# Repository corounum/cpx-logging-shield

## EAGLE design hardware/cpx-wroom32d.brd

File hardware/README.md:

## CPX Logging Shield

This "shield" for the Circuit Playground Express integrates:

* an ESP32 WROOM-32D module for capturing data via serial (or, eventually, I2C), storing that data (on the integrated 4MB flash), and presenting the data back via WiFi
* A BME680 temperature/pressure/VOC/eCO2 sensor
* A PCF8523 real time clock (for timestamping readings) and CR1220 battery (for clock retention)

In addition, a QUIIC connector is included for attaching Sparkfun-produced I2C modules. The bottom-mounted FTDI header can be soldered for development, and used as pogopin landing pads for production with the appropriate jig.

The board ONLY takes power from a connected CPX; it draws from VOUT, which is EITHER connected to USB or battery. The shield has its own AP2112 voltage regulator.

It is expected that the combination of a CPX and this shield might run for at most days. The shield attempts to sleep between readings, but it is known that this is potentially a "short life" sensing platform suitable for educational purposes, but not long-life monitoring in research contexts.

The following README text acknowledges that the board design herein leverages the excellent work of [Adafruit Industries](https://adafruit.com), and as a derivative work, is provided under a compatible, open license.

## Adafruit-Circuit-Playground-Express-PCB

PCB files for the Adafruit Circuit Playground Express

This is the PCB files for the Adafruit Circuit Playground
Format is EagleCAD schematic and board layout

For more details, check out the product page at

   * http://www.adafruit.com/products/3333

Adafruit invests time and resources providing this open source design, 
please support Adafruit and open-source hardware by purchasing 
products from Adafruit!

Designed by Adafruit Industries.  
Creative Commons Attribution, Share-Alike license, check license.txt for more information
All text above must be included in any redistribution

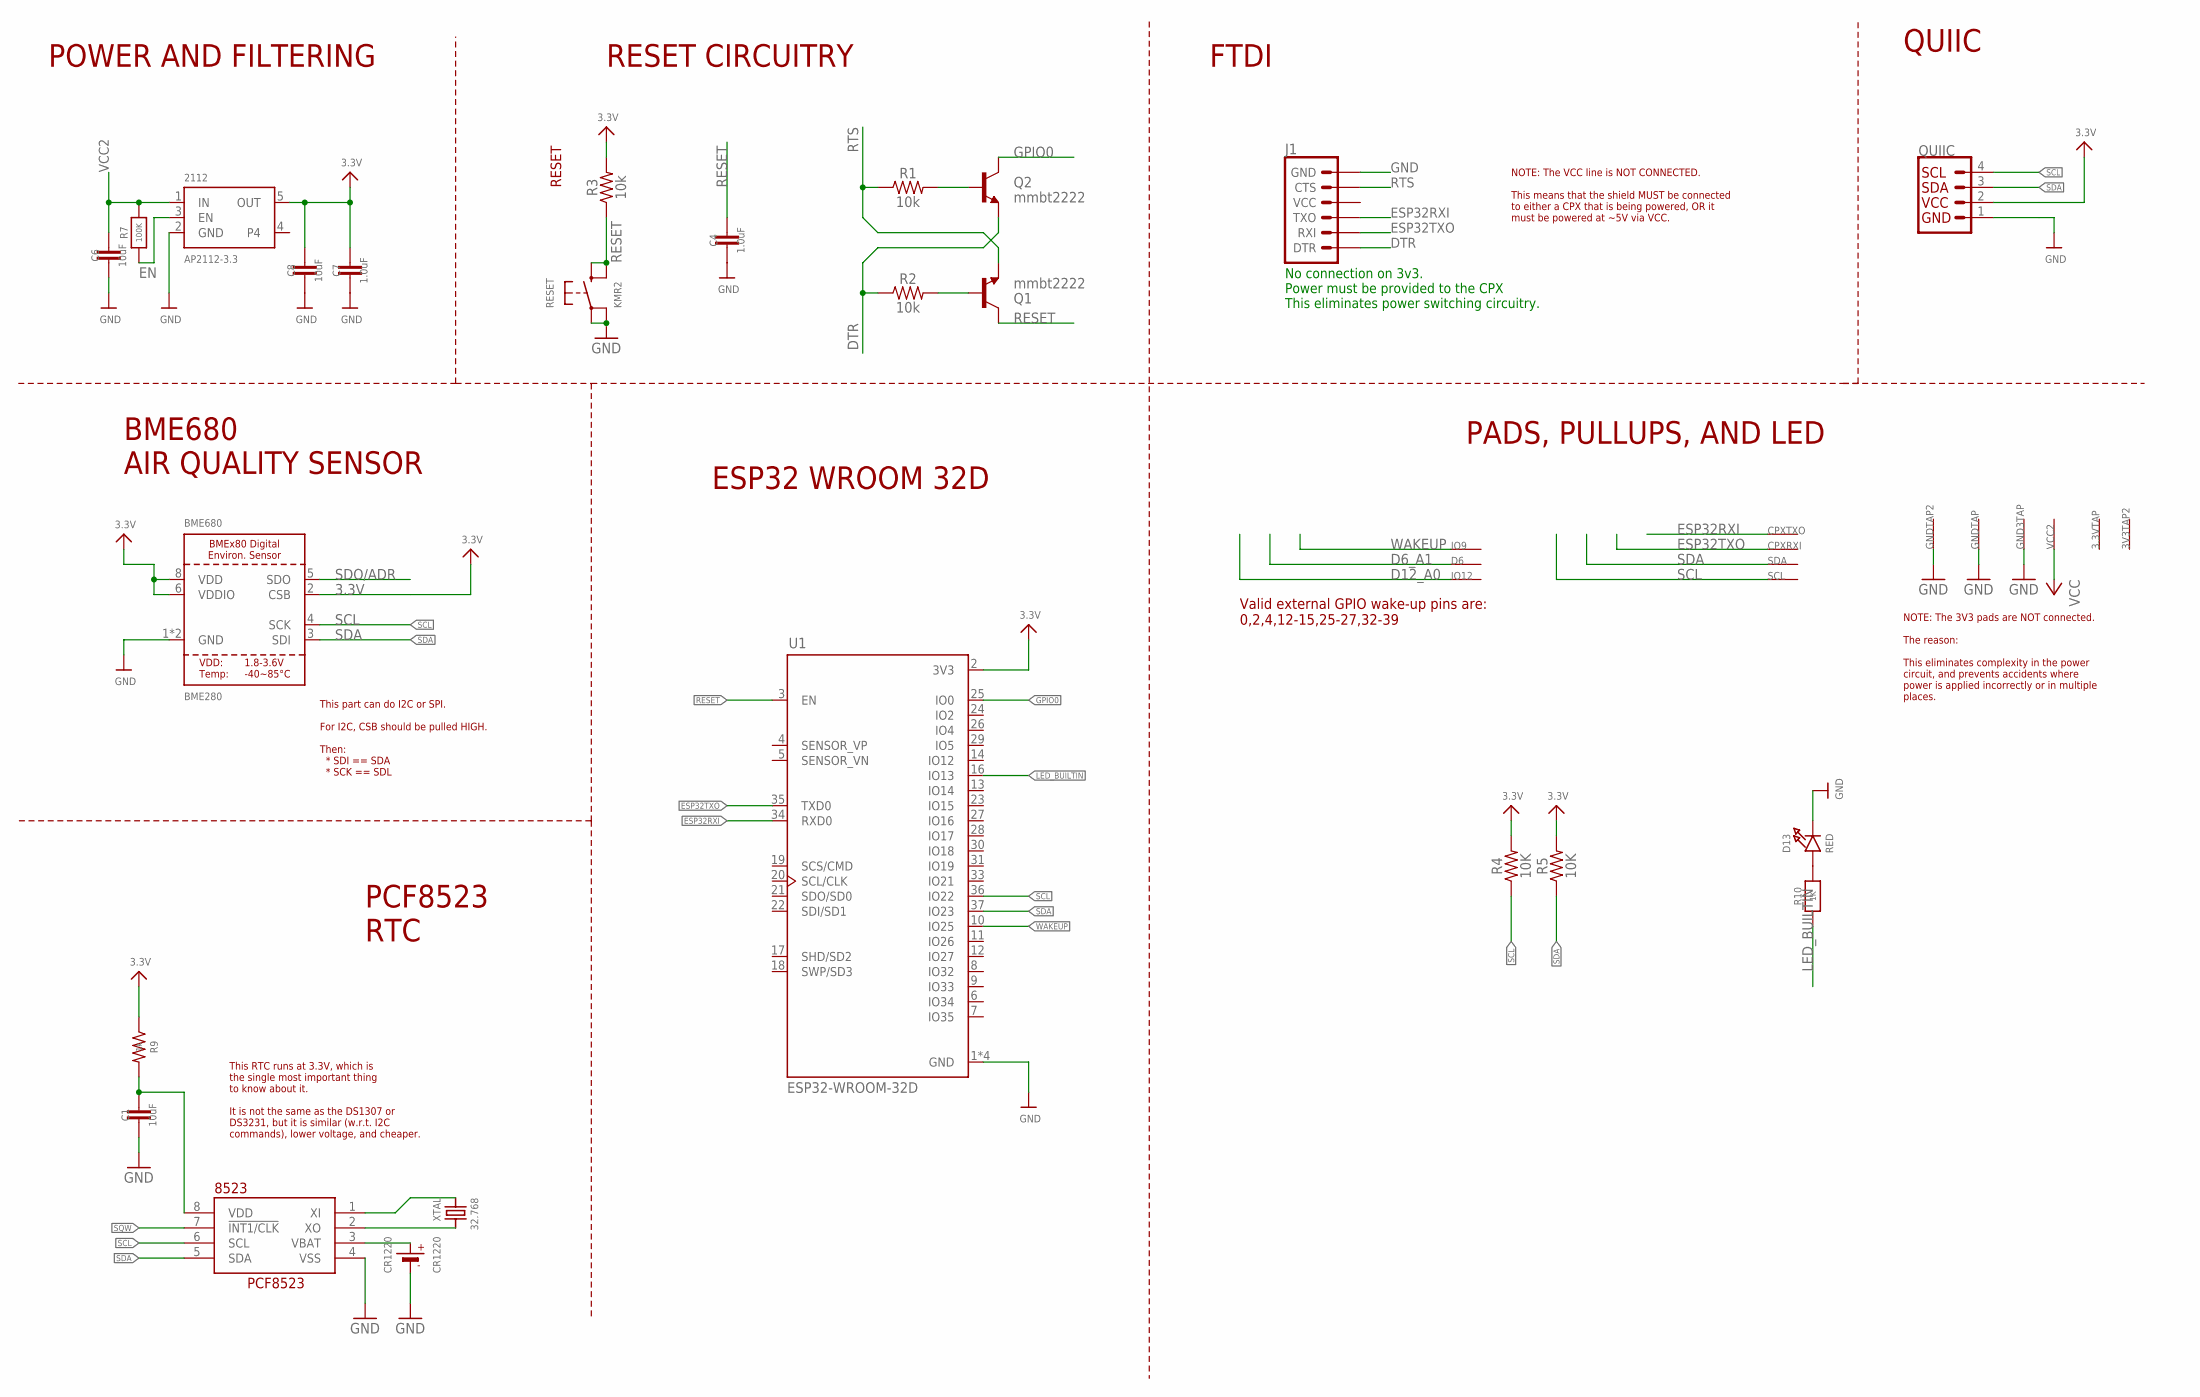
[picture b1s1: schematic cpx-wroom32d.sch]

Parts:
3.3VTAP, 3V3TAP2: SEWTAP-ALLIGATOR; SEWALLI
2112: AP2112-3.3; SOT23-5
8523: RTC_PCF8523T; SOIC8_150MIL
BME680: BME280
C1, C6, C8: 10uF; 0603
C4, C7: 1.0uF; 0603
CPXRXI: SEWTAP-ALLIGATOR; SEWALLI
CPXTXO: SEWTAP-ALLIGATOR; SEWALLI
CR1220: CR1220
D6: SEWTAP-ALLIGATOR; SEWALLI
D13: RED; CHIPLED_0805_NOOUTLINE
GND3TAP: SEWTAP-ALLIGATOR; SEWALLI
GNDTAP, GNDTAP2: SEWTAP-ALLIGATOR; SEWALLI
IO9, IO12: SEWTAP-ALLIGATOR; SEWALLI
J1: 6_PIN_SERIAL_TARGETRA_SMT; 6_PIN_SERIAL_TARGET_SIDE_RA_SMT
Q1, Q2: mmbt2222; SOT23-3
QUIIC: QWIIC_CONNECTORJS-1MM; 1X04_1MM_RA
R1, R2, R3: 10k; 0603
R4, R5: 10K; 0603
R7: 100K; 0603-NO
R9: 1k; 0603
R10: 1K; 0603-NO
RESET: KMR2; BTN_KMR2_4.6X2.8
SCL: SEWTAP-ALLIGATOR; SEWALLI
SDA: SEWTAP-ALLIGATOR; SEWALLI
U1: ESP32-WROOM-32D; MODULE_ESP32-WROOM-32D
VCC2: SEWTAP-ALLIGATOR; SEWALLI
XTAL: 32.768; CRYSTAL_8X3.8

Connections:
3.3V: 2112.5 (OUT), BME680.2 (CSB), BME680.6 (VDDIO), BME680.8 (VDD), C7.1, C8.1, QUIIC.2 (VCC), R3.2, R4.2, R5.2, R9.1, U1.2 (3V3)
CLKVCC: 8523.8 (VDD), C1.1, R9.2
D6_A1: D6.P$1
D12_A0: IO12.P$1
DTR: J1.1 (DTR), Q2.2 (E), R2.1
EN: 2112.3 (EN), R7.1
ESP32RXI: CPXTXO.P$1, J1.2 (TXO), U1.34 (RXD0)
ESP32TXO: CPXRXI.P$1, J1.3 (RXI), U1.35 (TXD0)
GND: 2112.2 (GND), 8523.4 (VSS), BME680.1 (GND), BME680.7 (GND), C1.2, C4.2, C6.2, C7.2, C8.2, CR1220.-, D13.C, GND3TAP.P$1, GNDTAP.P$1, GNDTAP2.P$1, J1.6 (GND), QUIIC.1 (GND), RESET.A, RESET.A' (P1), U1.1 (GND), U1.15 (GND), U1.38 (GND), U1.39 (GND)
GPIO0: Q2.3 (C), U1.25 (IO0)
LED_BUILTIN: R10.1, U1.16 (IO13)
unnamed: D13.A, R10.2
unnamed: Q1.1 (B), R2.2
unnamed: Q2.1 (B), R1.2
RESET: C4.1, Q1.3 (C), R3.1, RESET.B (S), RESET.B' (S1), U1.3 (EN)
RTS: J1.5 (CTS), Q1.2 (E), R1.1
SCL: 8523.6 (SCL), BME680.4 (SCK), QUIIC.4 (SCL), R4.1, SCL.P$1, U1.36 (IO22)
SDA: 8523.5 (SDA), BME680.3 (SDI), QUIIC.3 (SDA), R5.1, SDA.P$1, U1.37 (IO23)
SDO/ADR: BME680.5 (SDO)
SQW: 8523.7 (!INT1/CLK)
VBAT1: 8523.3 (VBAT), CR1220.+$1 (+)
VCC: VCC2.P$1
VCC2: 2112.1 (IN), C6.1, R7.2
WAKEUP: IO9.P$1, U1.10 (IO25)
XI: 8523.1 (XI), XTAL.P$1 (1)
XO: 8523.2 (XO), XTAL.P$4 (2)

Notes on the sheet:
RESET
No connection on 3v3. Power must be provided to the CPX This eliminates power switching circuitry.
POWER AND FILTERING
RESET CIRCUITRY
FTDI
ESP32 WROOM 32D
BME680 AIR QUALITY SENSOR
PCF8523 RTC
PADS, PULLUPS, AND LED
This part can do I2C or SPI. For I2C, CSB should be pulled HIGH. Then: * SDI == SDA * SCK == SDL
This RTC runs at 3.3V, which is the single most important thing to know about it. It is not the same as the DS1307 or DS3231, but it is similar (w.r.t. I2C commands), lower voltage, and cheaper.
NOTE: The VCC line is NOT CONNECTED. This means that the shield MUST be connected to either a CPX that is being powered, OR it must be powered at ~5V via VCC.
NOTE: The 3V3 pads are NOT connected. The reason: This eliminates complexity in the power circuit, and prevents accidents where power is applied incorrectly or in multiple places.
QUIIC
Valid external GPIO wake-up pins are: 0,2,4,12-15,25-27,32-39

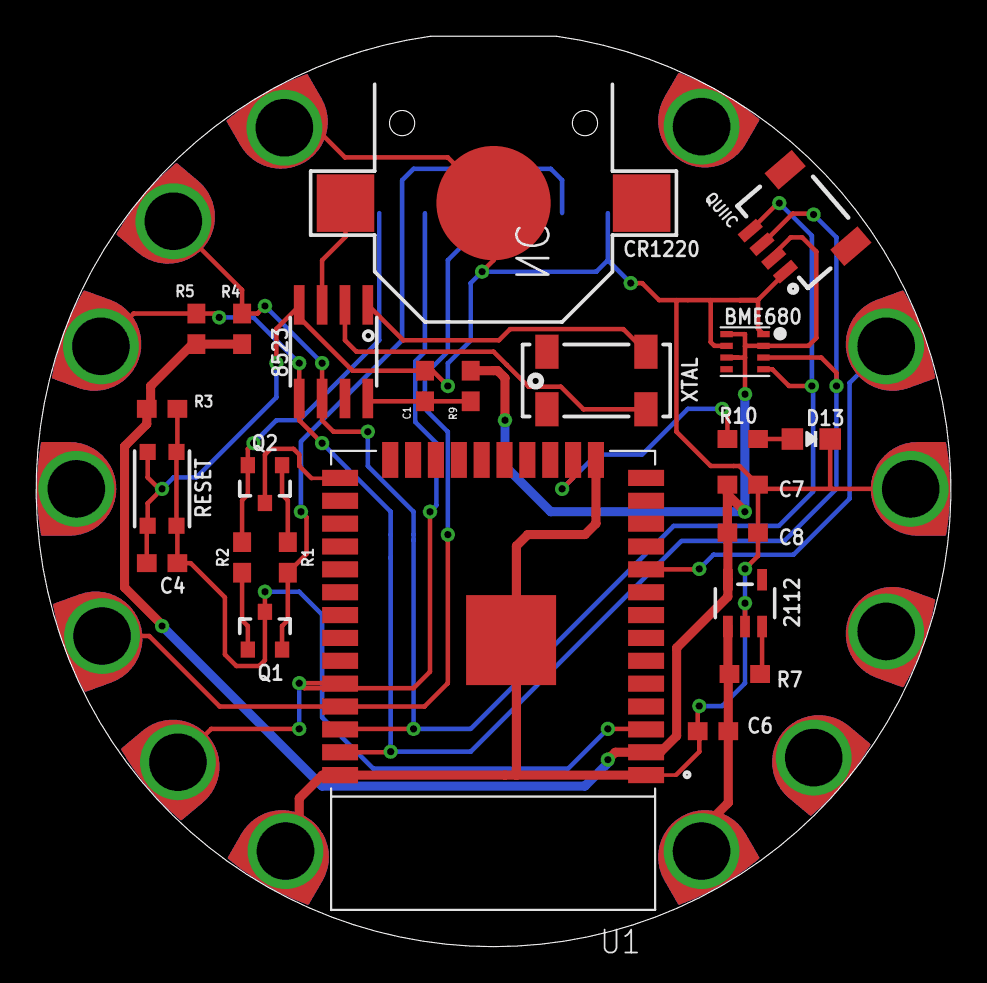
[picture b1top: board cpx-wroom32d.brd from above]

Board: 2 copper layers, 50.8 x 50.6 mm, 38 parts (1 on the bottom side), 21 nets.

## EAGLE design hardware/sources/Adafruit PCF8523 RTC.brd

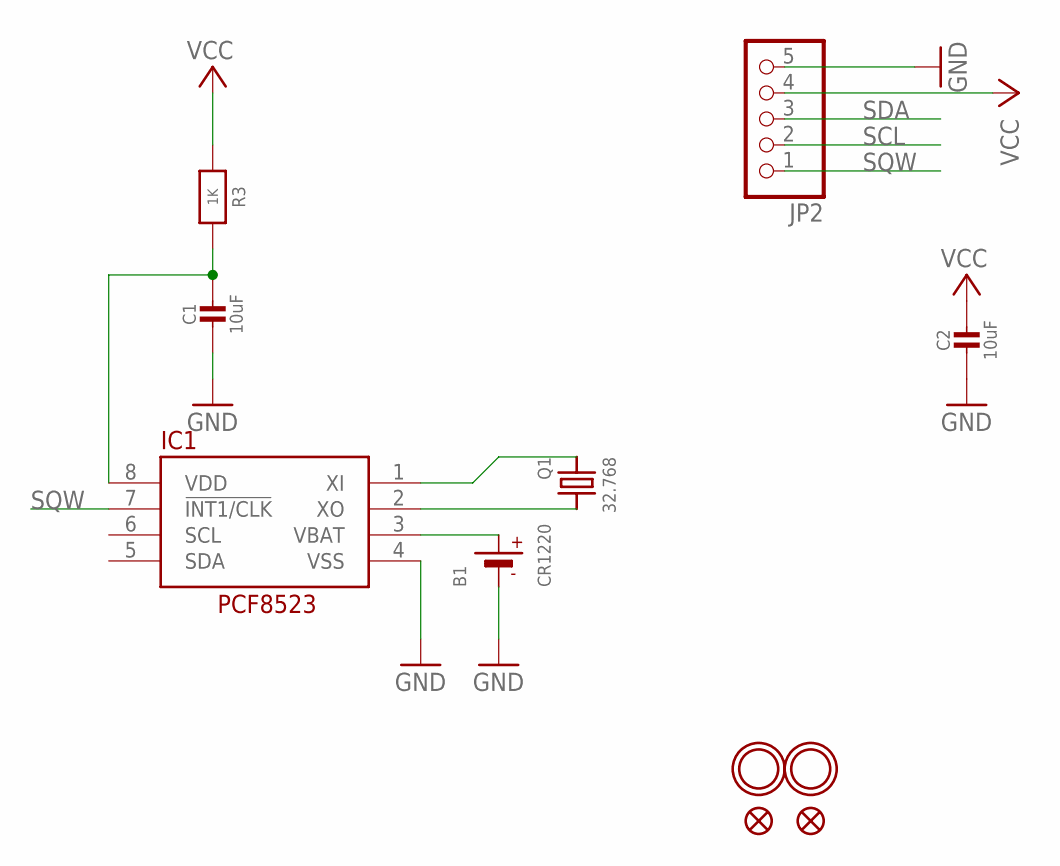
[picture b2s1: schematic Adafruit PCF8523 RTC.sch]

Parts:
B1: CR1220
C1, C2: 10uF; 0805-NO
FID1, FID2: FIDUCIAL""; FIDUCIAL_1MM
IC1: RTC_PCF8523T; SOIC8_150MIL
JP2: HEADER-1X576MIL; 1X05_ROUND_76
Q1: 32.768; CRYSTAL_8X3.8
R3: 1K; 0805-NO
U$1, U$4: MOUNTINGHOLE2.0; MOUNTINGHOLE_2.0_PLATED

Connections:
GND: B1.-, C1.2, C2.2, IC1.4 (VSS), JP2.5
unnamed: C1.1, IC1.8 (VDD), R3.2
unnamed: IC1.1 (XI), Q1.P$1 (1)
unnamed: IC1.2 (XO), Q1.P$4 (2)
SCL: JP2.2
SDA: JP2.3
SQW: IC1.7 (!INT1/CLK), JP2.1
VBAT: B1.+$1 (+), IC1.3 (VBAT)
VCC: C2.1, JP2.4, R3.1

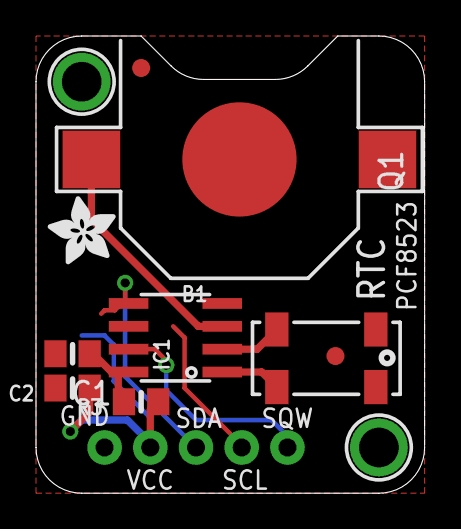
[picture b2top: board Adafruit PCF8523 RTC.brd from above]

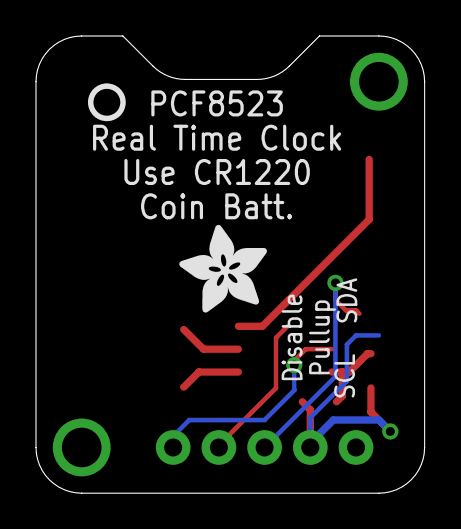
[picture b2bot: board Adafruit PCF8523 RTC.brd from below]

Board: 2 copper layers, 21.6 x 25.4 mm, 14 parts (2 on the bottom side), 7 nets.

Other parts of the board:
U$2: ADAFRUIT_3.5MM
U$3: PCBFEAT-REV-040
U$5: ADAFRUIT_5MM

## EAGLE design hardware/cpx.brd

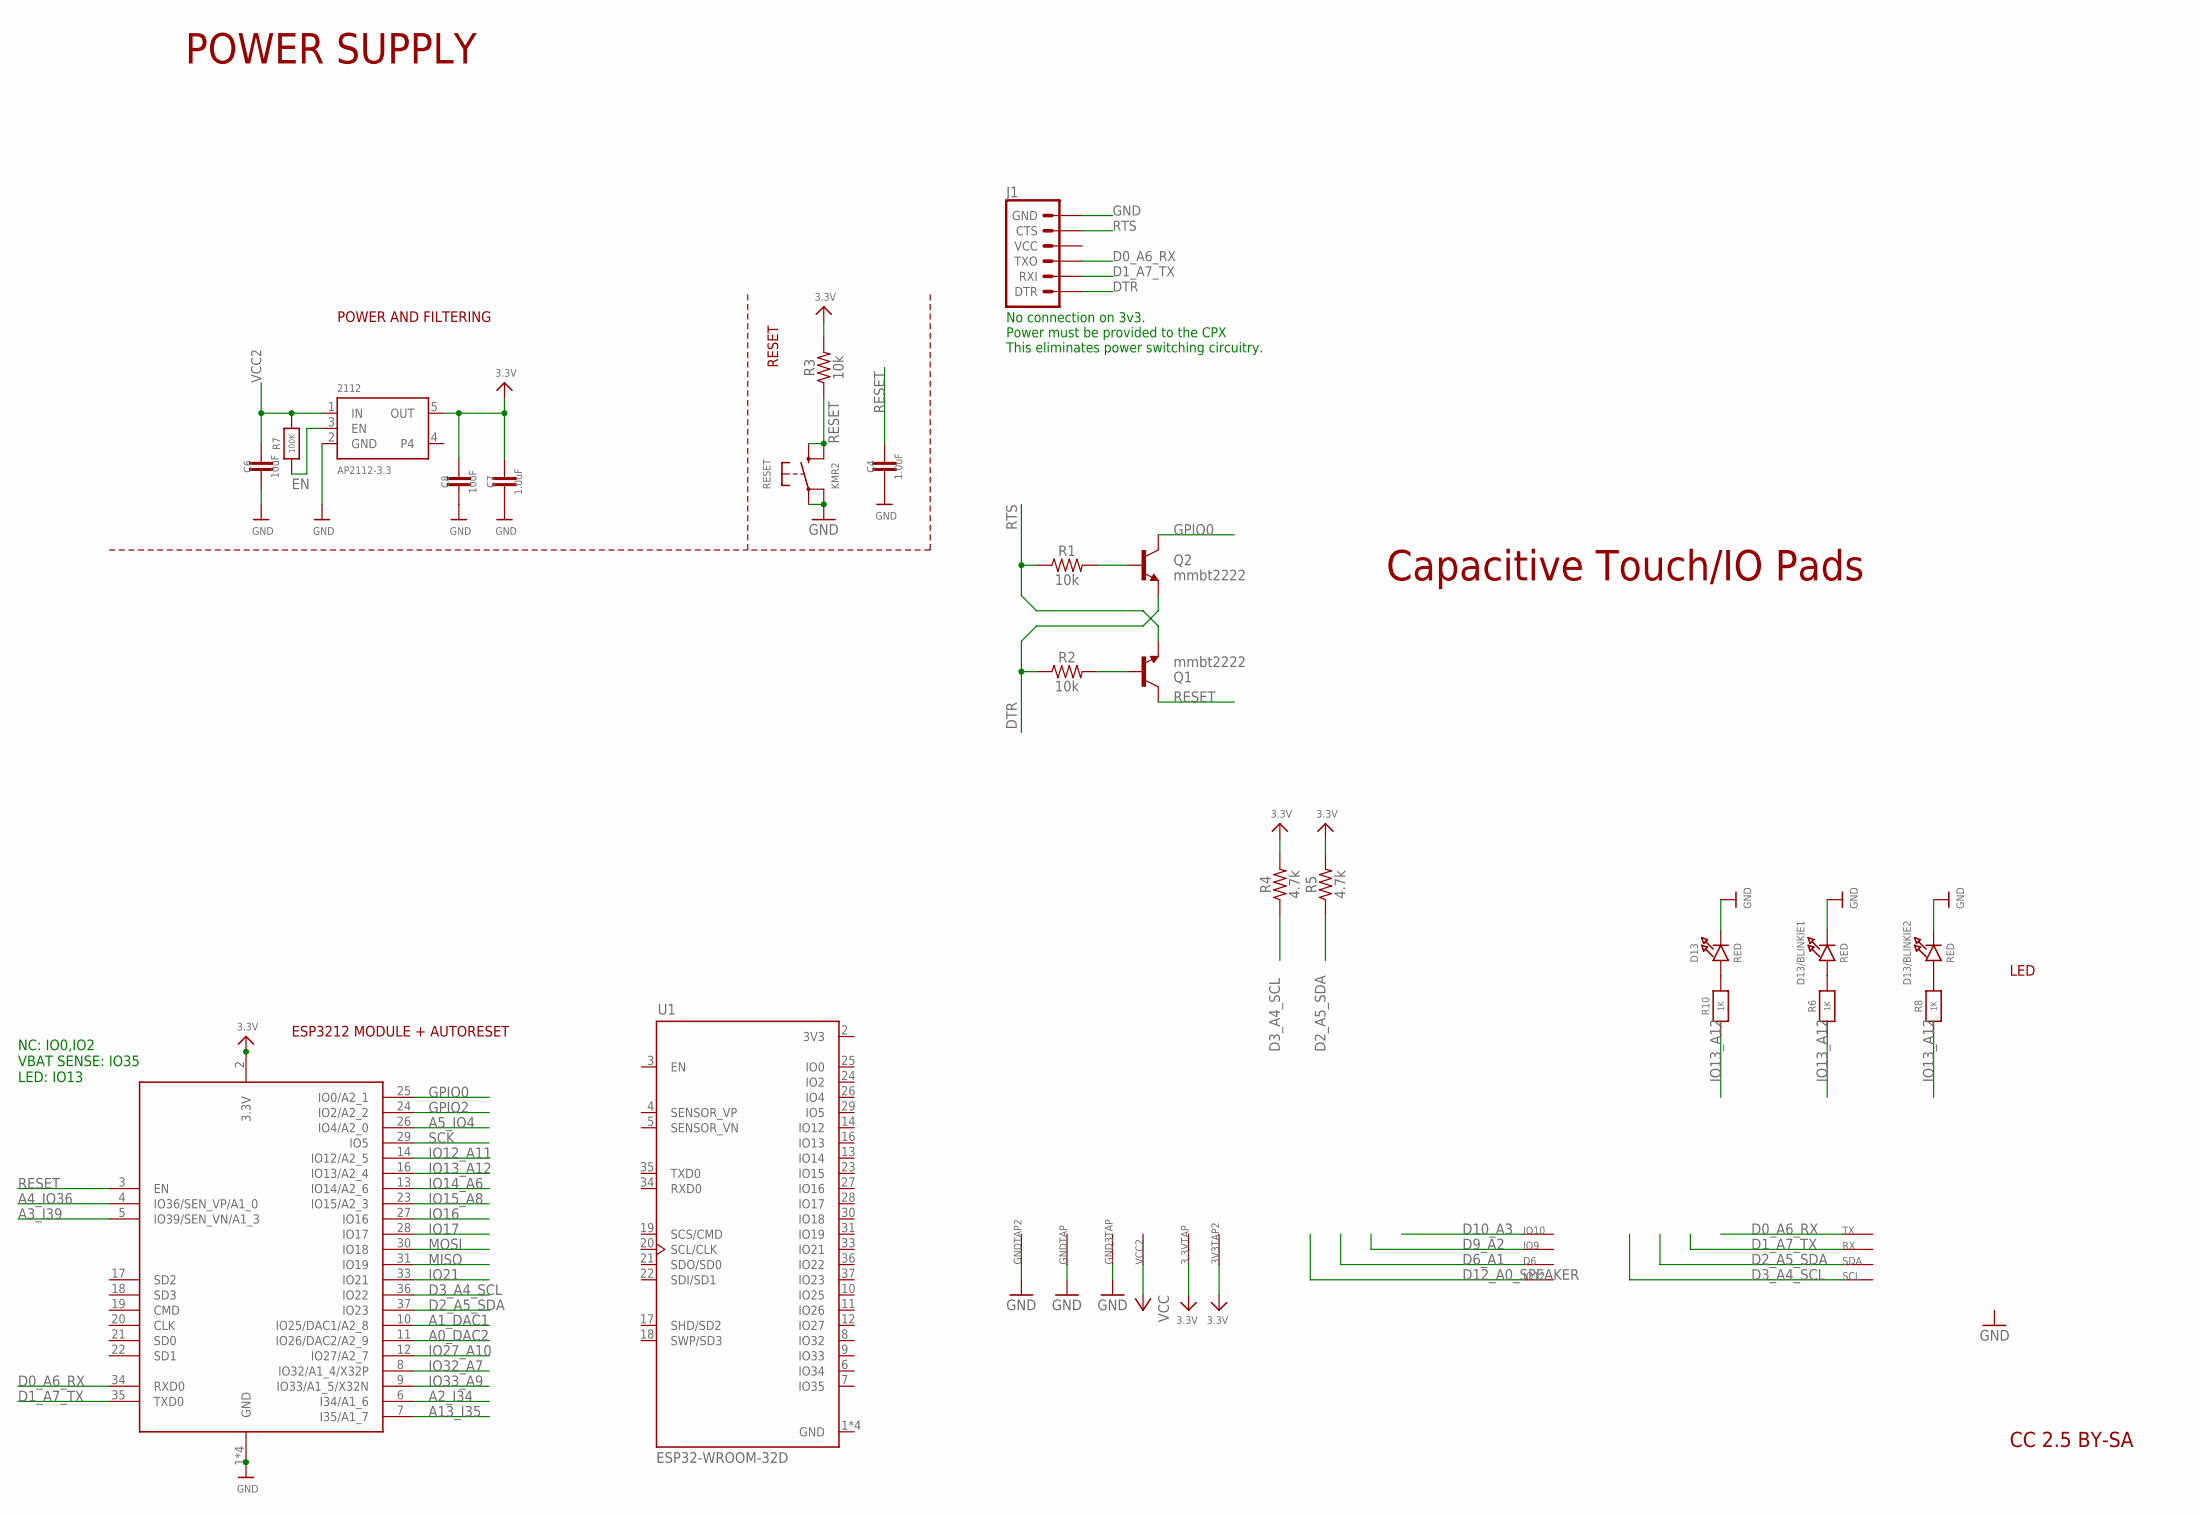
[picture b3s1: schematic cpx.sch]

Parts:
3.3VTAP, 3V3TAP2: SEWTAP-ALLIGATOR; SEWALLI
2112: AP2112-3.3; SOT23-5
C4, C7: 1.0uF; 0603
C6, C8: 10uF; 0603
D6: SEWTAP-ALLIGATOR; SEWALLI
D13, D13/BLINKIE1, D13/BLINKIE2: RED; CHIPLED_0805_NOOUTLINE
GND3TAP: SEWTAP-ALLIGATOR; SEWALLI
GNDTAP, GNDTAP2: SEWTAP-ALLIGATOR; SEWALLI
IO9, IO10, IO12: SEWTAP-ALLIGATOR; SEWALLI
J1: 6_PIN_SERIAL_TARGET; 1X06
Q1, Q2: mmbt2222; SOT23-3
R1, R2, R3: 10k; 0603
R4, R5: 4.7k; 0603
R6, R8, R10: 1K; 0603-NO
R7: 100K; 0603-NO
RESET: KMR2; BTN_KMR2_4.6X2.8
RX: SEWTAP-ALLIGATOR; SEWALLI
SCL: SEWTAP-ALLIGATOR; SEWALLI
SDA: SEWTAP-ALLIGATOR; SEWALLI
TX: SEWTAP-ALLIGATOR; SEWALLI
U1: ESP32-WROOM-32D; MODULE_ESP32-WROOM-32D
VCC2: SEWTAP-ALLIGATOR; SEWALLI
X2: ESP32_WROOM32_SKINNY; WROOM32_SKINNY

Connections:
3.3V: 3.3VTAP.P$1, 3V3TAP2.P$1, 2112.5 (OUT), C7.1, C8.1, R3.2, R4.2, R5.2, X2.2 (3.3V)
3V3: U1.2 (3V3)
A0_DAC2: X2.11 (IO26/DAC2/A2_9)
A1_DAC1: X2.10 (IO25/DAC1/A2_8)
A2_I34: X2.6 (I34/A1_6)
A3_I39: X2.5 (IO39/SEN_VN/A1_3)
A4_IO36: X2.4 (IO36/SEN_VP/A1_0)
A5_IO4: X2.26 (IO4/A2_0)
A13_I35: X2.7 (I35/A1_7)
D0_A6_RX: J1.3 (TXO), TX.P$1, X2.34 (RXD0)
D1_A7_TX: J1.2 (RXI), RX.P$1, X2.35 (TXD0)
D2_A5_SDA: R5.1, SDA.P$1, X2.37 (IO23)
D3_A4_SCL: R4.1, SCL.P$1, X2.36 (IO22)
D6_A1: D6.P$1
D9_A2: IO9.P$1
D10_A3: IO10.P$1
D12_A0_SPEAKER: IO12.P$1
DTR: J1.1 (DTR), Q2.2 (E), R2.1
EN: 2112.3 (EN), R7.1
GND: 2112.2 (GND), C4.2, C6.2, C7.2, C8.2, D13.C, D13/BLINKIE1.C, D13/BLINKIE2.C, GND3TAP.P$1, GNDTAP.P$1, GNDTAP2.P$1, J1.6 (GND), RESET.A, RESET.A' (P1), U1.1 (GND), U1.15 (GND), U1.38 (GND), U1.39 (GND), X2.1 (GND), X2.15 (GND), X2.38 (GND), X2.P$1 (GND)
GPIO0: Q2.3 (C), X2.25 (IO0/A2_1)
GPIO2: X2.24 (IO2/A2_2)
IO12_A11: X2.14 (IO12/A2_5)
IO13_A12: R6.1, R8.1, R10.1, X2.16 (IO13/A2_4)
IO14_A6: X2.13 (IO14/A2_6)
IO15_A8: X2.23 (IO15/A2_3)
IO16: X2.27 (IO16)
IO17: X2.28 (IO17)
IO21: X2.33 (IO21)
IO27_A10: X2.12 (IO27/A2_7)
IO32_A7: X2.8 (IO32/A1_4/X32P)
IO33_A9: X2.9 (IO33/A1_5/X32N)
MISO: X2.31 (IO19)
MOSI: X2.30 (IO18)
unnamed: D13/BLINKIE1.A, R6.2
unnamed: D13/BLINKIE2.A, R8.2
unnamed: D13.A, R10.2
unnamed: Q1.1 (B), R2.2
unnamed: Q2.1 (B), R1.2
RESET: C4.1, Q1.3 (C), R3.1, RESET.B (S), RESET.B' (S1), X2.3 (EN)
RTS: J1.5 (CTS), Q1.2 (E), R1.1
SCK: X2.29 (IO5)
VCC: VCC2.P$1
VCC2: 2112.1 (IN), C6.1, R7.2

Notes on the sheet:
CC 2.5 BY-SA
POWER SUPPLY
Capacitive Touch/IO Pads
POWER AND FILTERING
RESET
LED
ESP3212 MODULE + AUTORESET
NC: IO0,IO2 VBAT SENSE: IO35 LED: IO13
No connection on 3v3. Power must be provided to the CPX This eliminates power switching circuitry.

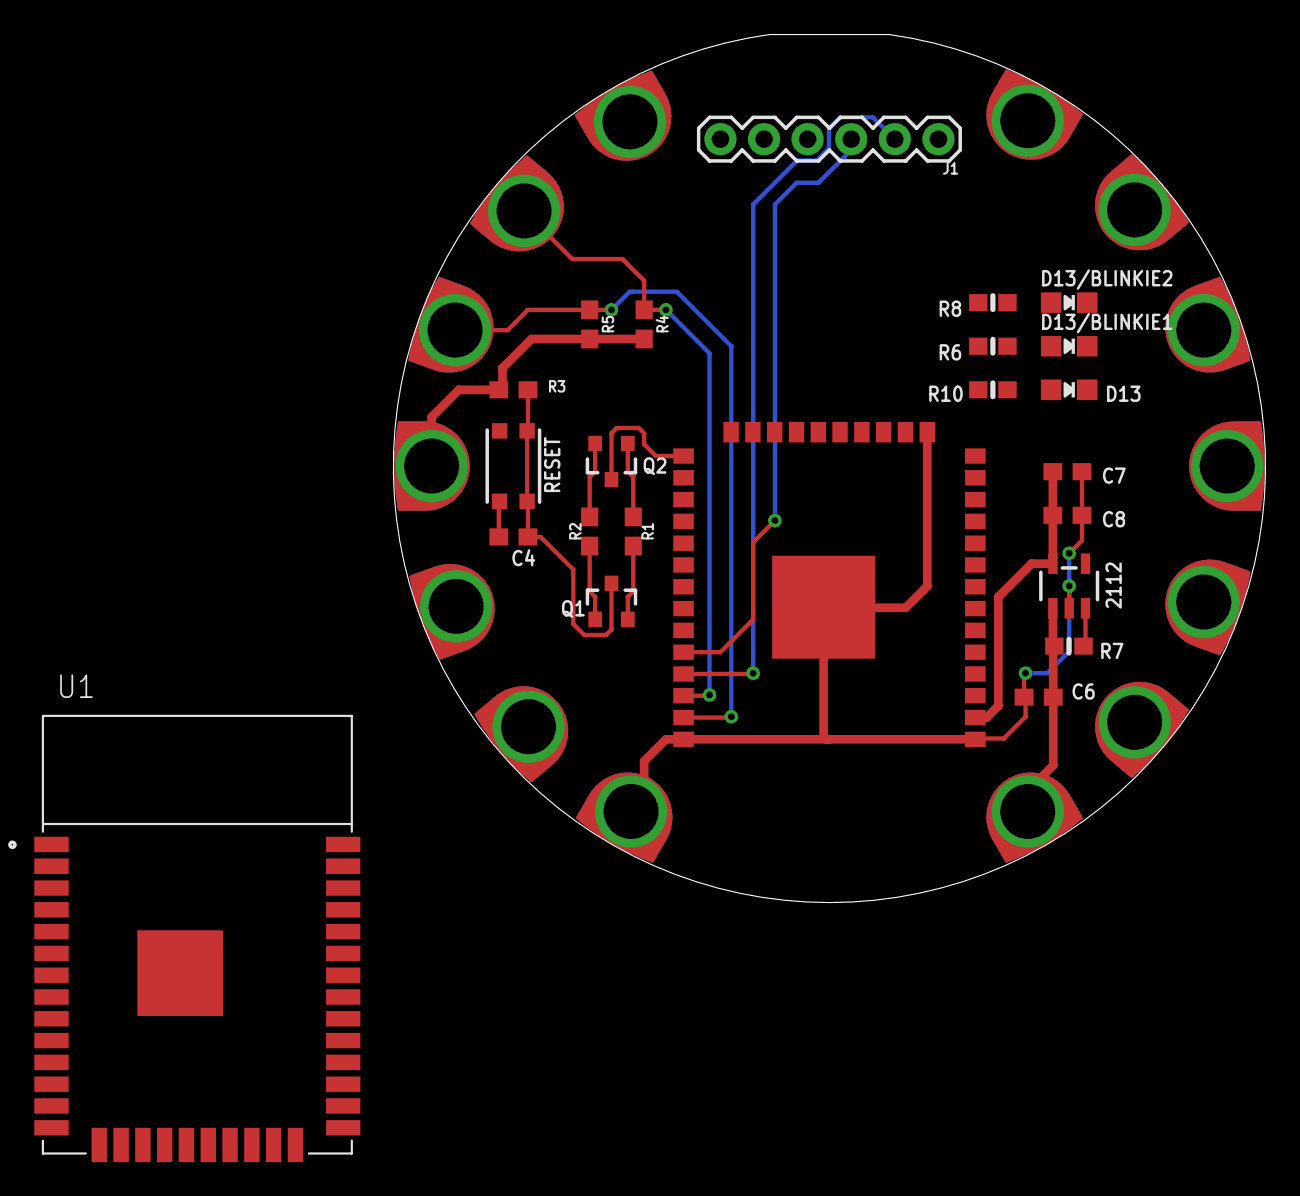
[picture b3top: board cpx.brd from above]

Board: 2 copper layers, 50.8 x 50.6 mm, 39 parts (1 on the bottom side), 18 nets.

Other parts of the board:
U$16: CPLAY_EXPRESS_FRONT_REVG
U$46: CPLAY_EXPRESS_BACK_REVD

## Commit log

2019-06-22 First commit.
    This should have been under version control a long time ago.
2019-06-22 About to remove some connections to the CPX.
2019-06-22 Routed.
2019-06-22 Looks goo.
2019-06-22 Cleaned up labeling, schematic.
2019-06-22 Removing the old version.
2019-06-22 Moving things around.
2019-06-22 Update the hardware readme.
2019-06-22 Add note about pads.
2019-06-22 Newline.
2019-06-23 Adding in my MicroPython explorations.
    Testing that things work, basically. Nothing focused yet.
2019-06-23 Forgot .gitignore, updates.
    * Added a wakeup line to A2 on the CPX.
    Toggling this is to trigger the external interrupt on
    the ESP32. This seems better than playing games with RX/TX
    * Moved BME680 a bit, to get it away from the QUIIC connector.
    * Exploring sleep. Need to think about what I want for a serial protocol. Line-oriented? Byte-oriented?
    I'd rather we were using I2C for this, but for the team, we're using Python.
2019-06-23 Byte protocol explored.
    I'm ready to talk through this with the students.

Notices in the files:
parts and their libraries:
microbuilder: This work is placed in the public domain, and may be freely used for commercial and non-commercial work with the following conditions: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
SparkFun: Licensing: CC v3.0 Share-Alike You are welcome to use this library for commercial purposes.
